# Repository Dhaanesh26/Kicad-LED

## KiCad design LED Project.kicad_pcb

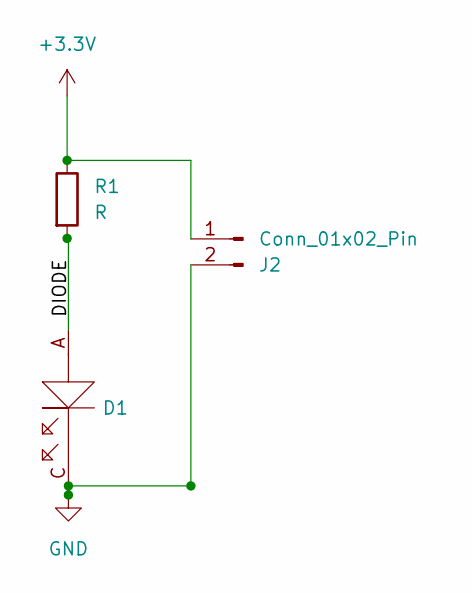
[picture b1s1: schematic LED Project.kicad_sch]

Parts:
D1: LED0603
J2: Conn_01x02_Pin; Molex_KK-254_AE-6410-02A_1x02_P2.54mm_Vertical
R1: R; R_0805_2012Metric

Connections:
+3.3V: J2.1, R1.1
GND: D1.C (Cathode), J2.2
unnamed: D1.A (Anode), R1.2

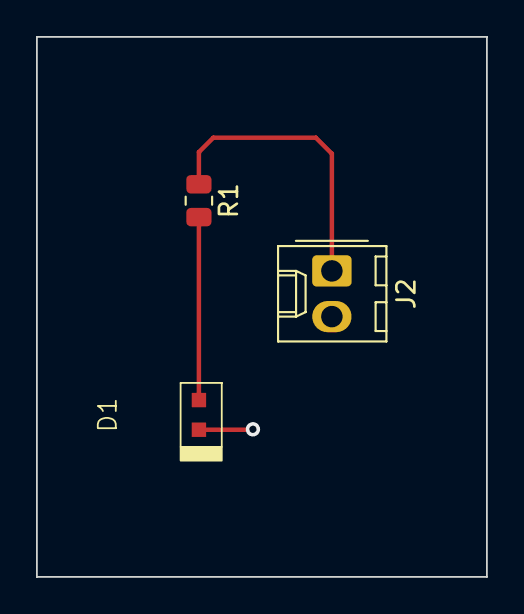
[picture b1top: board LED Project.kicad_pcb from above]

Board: 2 copper layers, 25.0 x 30.0 mm, 3 parts (0 on the bottom side), 3 nets.

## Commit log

2023-08-29 ster
